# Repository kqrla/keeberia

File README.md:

# keeberia ☆.ᐟ

> a visual, parametric way to design custom macropads, keyboards, and other little physical input devices without manually rebuilding the same stuff every single time»

## what is this

keeberia is basically me trying to make the process of making a keyboard less annoying. <br>
for context, i loooove keyboards, and i've made end-to-end macropad pcbs + cases before, and while making them is really fun, there is also a very specific point each type where i'm like *"ugh. there's got to be a better way than this"* because so much of the process is repetitive, which, my adhd be damned, feels like walking on legos to me. i mean, come on, we

- have a layout.
- place switches.
- place their footprints.
- make the matrix.
- route it.
- then you go make a plate.
- then you go make a case.
- then you add screw holes.
- then you add standoffs.
- then you make sure the usb port isn't blocked.
- then you realize you changed the pcb layout.
- so now you have to go fix the case.
- and then you change the switch.
- and now the clearance is different.
- and then you have to fix something else.

none of these things are necessarily difficult individually. the annoying part is that the same information keeps having to be translated between different programs and rebuilt manually.

and keyboards are structured enough that a LOT of this could just be generated.

so... why not?

---

## the problem

custom keyboard design currently involves a weird collection of tools that each know about one part of the device.

you might use:

- kicad for the pcb
- fusion 360 / onshape / openscad / etc. for the case
- another thing for firmware
- another thing for keycap models
- spreadsheets for parts
- manufacturer tools for production
- random websites for component footprints and references

and then somehow the person making the keyboard is responsible for making sure all of those things agree with each other.

- the layout knows where the keys are.
- the pcb knows where the footprints are.
- the cad file knows where the case is.
- the keycap knows how tall it is.

but they don't necessarily know about each other.

so the human becomes the middleware.

which feels kind of silly when the relationships are often extremely predictable.

---

## the repetitive part

this is the part that really bothers me.

- a switch has a footprint.
- a switch has a known spacing.
- a 2u key has predictable geometry.
- an encoder has predictable mounting requirements.
- a display has predictable dimensions.
- a usb connector needs a predictable opening.
- a screw needs a hole.
- a standoff needs somewhere to go.
- a case needs clearance around the pcb.

these are not random artistic decisions.

they're relationships.

and computers are very good at relationships.

- if i move something, the other things that depend on it should know that i moved it.
- if i change my switch type, the pcb and case should know that too.
- if i make my pcb wider, my case should not sit there pretending it didn't happen.

---

## what keeberia is trying to do

keeberia is a design environment where you describe the device at a higher level and let the boring/repetitive parts get generated from that.

instead of starting with:

*"place footprint + assign net + route trace + draw wall + cut hole + measure clearance"*

you start with:

*"i want a 4x4 macropad"*

then:

- «this is a knob»
- «these two spaces are an eink display»
- «these are choc switches»
- «i want rgb»
- «i want a weird shaped pcb»
- «i want a chunky case»

and keeberia figures out how those decisions translate into the actual hardware.

---

# the five flows

keeberia is split into five major design flows.

they aren't meant to be five separate files or five completely separate programs.

they're five ways of looking at the same device.

```
layout
  ↓
components
  ↓
pcb
  ↓
case
  ↓
keys + knobs
```

but you can jump between them whenever you want.

- if you change something in components, the pcb and case should update.
- if you change the pcb shape, the case should react.
- if you change the keycap profile, the 3d preview should change.

the project is one object. the flows are just different views into it.

---

## the first flow — layout

this is the "where does everything go" part.

you can start with something like:

- 2x2
- 3x3
- 4x4
- numpad
- blank

or start blank and use a google-docs-style grid selector.

once you're in the editor, every space starts as a key.

```
□ □ □ □
□ □ □ □
□ □ □ □
```

you can drag-select cells, merge them, split them, or right click them and do something like:

```
switch to →
    key
    encoder
    knob
    oled
    eink
    joystick
    spacer
```

so if i select two cells and turn them into an eink display, keeberia knows that those two cells are now one physical region.

this stage is deliberately not pcb design.

i just want to figure out the shape and arrangement of the device first.

---

## the second flow — components

now we figure out what everything actually is.

the layout might know that something is a key.

components tells keeberia:

- "okay, this is a cherry mx switch"
- "this is a kailh choc v1"
- "this is an ec11 encoder"
- "this is a 128x64 oled"

this is where you choose things like:

- switch type
- hotswap / solder
- stabilizers
- encoder model
- display model
- controller
- rgb
- other hardware

the ui should feel very notion-ish here.

select one thing, or select 12 things, then change a property.

for example:

```
switch

[ cherry mx ]
[ choc v1 ]
[ choc v2 ]
[ gateron low profile ]
```

then:

```
mounting

[ solder ]
[ hotswap ]
```

then:

```
rgb

[ none ]
[ per-key ]
[ underglow ]
```

and if i select every key, i should be able to change all of them at once.

the important part is that users don't have to know the footprint implementation just to choose a component.

if i choose an ec11, keeberia should know what an ec11 requires.

---

## the third flow — pcb

this is where the abstract design becomes an actual board.

the user should be able to control things like:

- pcb shape
- rounded corners
- custom dxf outlines
- silkscreen
- text
- graphics
- logos
- front/back artwork

but i don't want the first experience to be:

"congratulations, here are 900 traces"

the repetitive pcb work should be generated from the component information.

keeberia already knows:

- where the switches are
- what switches they are
- where the encoder is
- what encoder it is
- where the display is
- what controller is being used

so it should be able to use that information to generate the pcb structure.

advanced users can still expose traces, vias, nets, etc.

i just don't want every person making a tiny macropad to have to manually deal with everything.

---

## the forth flow — case

this is probably where the whole idea gets even more useful.

cases are so repetitive.

a lot of them are basically some variation of:

```
pcb
+
clearance
+
walls
+
mounting
+
cutouts
```

so instead of manually modeling the whole thing every time, keeberia should generate the geometry parametrically.

you choose things like:

- tray mount
- sandwich
- top mount
- integrated plate
- wall thickness
- pcb margin
- front/rear height
- typing angle
- screw type
- heatset inserts
- usb cutout
- reset access
- feet

and the case updates.

- if the pcb changes, the case changes.
- if the encoder moves, its opening moves.
- if the usb moves, the cutout moves.

that's the whole point.

---

## 05 — keys + knobs

and then we get to the fun part.

this is basically:

«okay now make the thing look and feel how i actually want it to»

choose keycap profiles:

- cherry
- oem
- dsa
- xda
- sa
- mt3
- choc

choose legends. choose knob styles. change knob diameter/height.

and see the actual finished device in the preview.

---

## the preview

the preview is not just some little thumbnail in the corner.

i want the device to basically live in the middle of the application.

there should be a 2d and 3d view.

2d is useful for:

- layout
- pcb
- silkscreen
- case dimensions
- exact placement

3d is useful for:

- case shape
- component clearance
- keycap profiles
- knobs
- overall appearance

and then there can be an exploded view:

```
keycaps
↓
switches
↓
plate
↓
pcb
↓
case
```

so you can actually see how the thing goes together.

the preview should be powered by the same underlying project data as the generators, so it isn't just a pretty fake rendering.

---

## the part i care about most

keeberia should understand that these things are related.

if i change:

```
mx → choc
```

that can affect:

- footprint
- plate
- switch height
- keycap clearance
- case height

if i change:

```
3x3 → 4x3
```

that can affect:

- pcb dimensions
- case dimensions
- mounting locations
- plate
- preview

if i move an encoder:

- its pcb footprint moves
- its case opening moves
- its knob moves in 3d

i don't want to manually tell five different programs that i moved something.

that's what the project model is for.

---

## under the hood

**autorouting is a two-rung ladder.** rung one is circuitron's own a* router — fast, in-process, deterministic. when a board is too dense for it, the worker escalates to [freerouting](https://freerouting.org) (open source, battle-tested push-and-shove) through a dsn/ses bridge: the board exports to specctra dsn at kicad's exact conventions, freerouting routes it headless, and the ses session imports back into the engine's own segment/via model — then judged by the same drc as the engine's routes. wire it up with `FREEROUTING_BIN` (jar or binary) and optional `FREEROUTING_JAVA` + `FREEROUTING_TIMEOUT_MS`; the rung is skipped cleanly when unset.

**all rendering happens on the viewer's hardware.** previews are client-side webgl/three.js computed from the same project model the generators consume — the server never touches a gpu.

keeberia isn't trying to reinvent every existing hardware tool.

it's more like a layer on top of them.

for pcb generation, the target is kicad-compatible output and eventually things like:

- kicad projects
- gerbers
- drill files
- bom
- pick-and-place files

for cad:

- openscad (parametric, printable — the tradeoffs are on record in [backend/cad/stack/tradeoffs.md](backend/cad/stack/tradeoffs.md))
- stl
- 3mf
- dxf

for the browser preview:

- three.js / webgl

the idea is basically:

```
my design
    ↓
keeberia project model
    ↓
pcb / cad / manufacturing / preview
```

rather than manually keeping all of those things synchronized.

---

## why start with keyboards?

because this is a really good problem to attack with software.

the keyboard ecosystem is already incredibly modular.

you have:

- switches
- keycaps
- pcbs
- plates
- cases
- encoders
- displays
- controllers
- leds
- stabilizers
- knobs
- cables
- artisan parts
- diy kits
- 3d printed parts
- cnc parts

people are already designing and buying all of these things.

there's a huge amount of customization happening.

and yet the actual design workflow still involves a lot of manual work.

that's kind of the opportunity.

---

## and it doesn't have to stay keyboards

the more i think about it, the less this is really a "keyboard tool."

a macropad is just one example of a customizable physical input device.

the same system could eventually work for:

- midi controllers
- stream deck-style devices
- simulator panels
- synth controllers
- custom desktop controllers
- accessibility interfaces
- maker electronics
- weird little one-off control panels

the common thing is basically:

```
inputs
+
electronics
+
physical layout
+
enclosure
```

which is exactly the kind of thing a parametric system can handle.

---

## what i want keeberia to feel like

- not kicad in a browser.
- not fusion 360 but worse.
- not another form where i have to enter 700 dimensions.

i want it to feel like:

"i have a weird little device idea"

and then i can just start making it.

- drag some squares around.
- turn one into a knob.
- merge two into a display.
- pick some switches.
- draw a weird pcb shape.
- make a case.
- put stupid little keycaps on it.
- rotate it in 3d.

then eventually hit:

export

and get the actual files needed to build the thing.

because if the computer can already figure out the boring, repetitive relationships between all of these parts, i would much rather let it do that and spend my time on the parts that are actually fun.

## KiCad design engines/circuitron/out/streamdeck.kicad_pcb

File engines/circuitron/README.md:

# circuitron

**circuitron** — the pcb + schematic engine. the deterministic pcb generator. typescript, zero runtime deps. **no ai anywhere in here** — same layout in, same board out, every time.

## fab rules drive the board

the generator's clearances and drc thresholds come from the fab's evidence
record, `research/manufacturing/capabilities/<id>.json`. pass a fab and the
board is generated and checked against that fab's published floors:

```ts
generatePcb(layout, "engine", { id: "jlcpcb", record: jlcpcbJson })
```

rules of the road:

- no fab selected = the engine's own floors, the pre-fab behaviour exactly
- a fab never loosens the engine, only tightens it. route constants clamp to
  engine floors so validated boards do not move silently, while drc
  thresholds take the fab's real published numbers (spacing, edge, trace
  width, via annular ring, plate drills) and the outline is measured against
  the fab's panel window
- the engine stays pure: it never reads files, the caller passes the record
- the first thing this caught: engine vias were 0.7mm over a 0.35mm drill, a
  0.175mm annular ring, under jlcpcb's own 0.20 minimum. vias are now 0.85mm
  (0.25 annular) and the engine drc refuses anything thinner

`test/fab.ts` runs all five fab records against all four reference boards.

## independent verification

`test/kicad_drc.ts` asks `kicad-cli` for a second opinion on the exported
board. it runs on the server/ci image only and skips cleanly when the binary
is absent. nobody using keeberia needs kicad: the browser sends a layout, the
daemon generates, and this gate runs before a human can order the artifacts.

## structure vs taste, and the downloads

the pipeline knows two kinds of input. structure (placements, nets, copper,
clearances) is engine owned and verified. taste (silhouette as rect, polygon
or uploaded dxf, decorative cutouts, silkscreen art) is user owned and
validated against the same fab record, never allowed to loosen a rule. see
`docs/pcb-artifacts.md` for the seam.

three downloads come out of every board: `.step` (planar brep, verified by
reading it back through occt), `.glb` (glTF 2.0, metres), `.stl` (binary,
millimetres). `src/step.ts`, `src/mesh3d.ts`.

## pipeline

```
keeberia layout json
  → layout.ts     placement: grid cells → components, mcu, holes, outline bbox
  → netlist.ts    direct-gpio or diode-matrix fallback, i2c/encoder budgets
  → route.ts      fan-out stubs + negotiated-congestion a* (0.5mm grid, keepouts, vias)
  → kicad.ts      kicad 8 .kicad_pcb export (s-expressions via sexp.ts)
  → drc.ts       pad clearance, shorts, edge, unrouted nets
  → bom.ts        bom csv        → silkscreen.ts   → preview.ts (svg)
```

entry: `generatePcb(layout, router?, fab?)` → `{ kicadPcb, bom, qmkInfo, result, fab }` (see `src/index.ts`).

## run tests

```bash
cd engines/circuitron
npx tsx test/run.ts        # 3 boards: hackpad-3key, ninepad, streamdeck → out/
npx tsx test/validate.ts   # s-expression balance + net/pad reference checks
npx tsx test/render.ts     # svg renders
```

## source layout

- `src/footprints.ts` — **the only place pad geometry lives**, verified against kicad official / hackclub care package / perigoso. provenance in `../research/`
- `src/types.ts` — layout schema + internal types (FootprintDef, Placement, Net…)
- `test/layouts.ts` — the three reference layouts (hackpad-3key, ninepad, streamdeck); regression fixtures — the autolayout daemon smoke-tests against these too

## rules

- new parts get footprint-verified (three sources or datasheet) **before** entering `footprints.ts`
- the router never gets to leave the board edge (0.45mm inside) — drc and router agree on this
- output determinism is a feature: no timestamps, no randomness, no map-iteration-order leaks

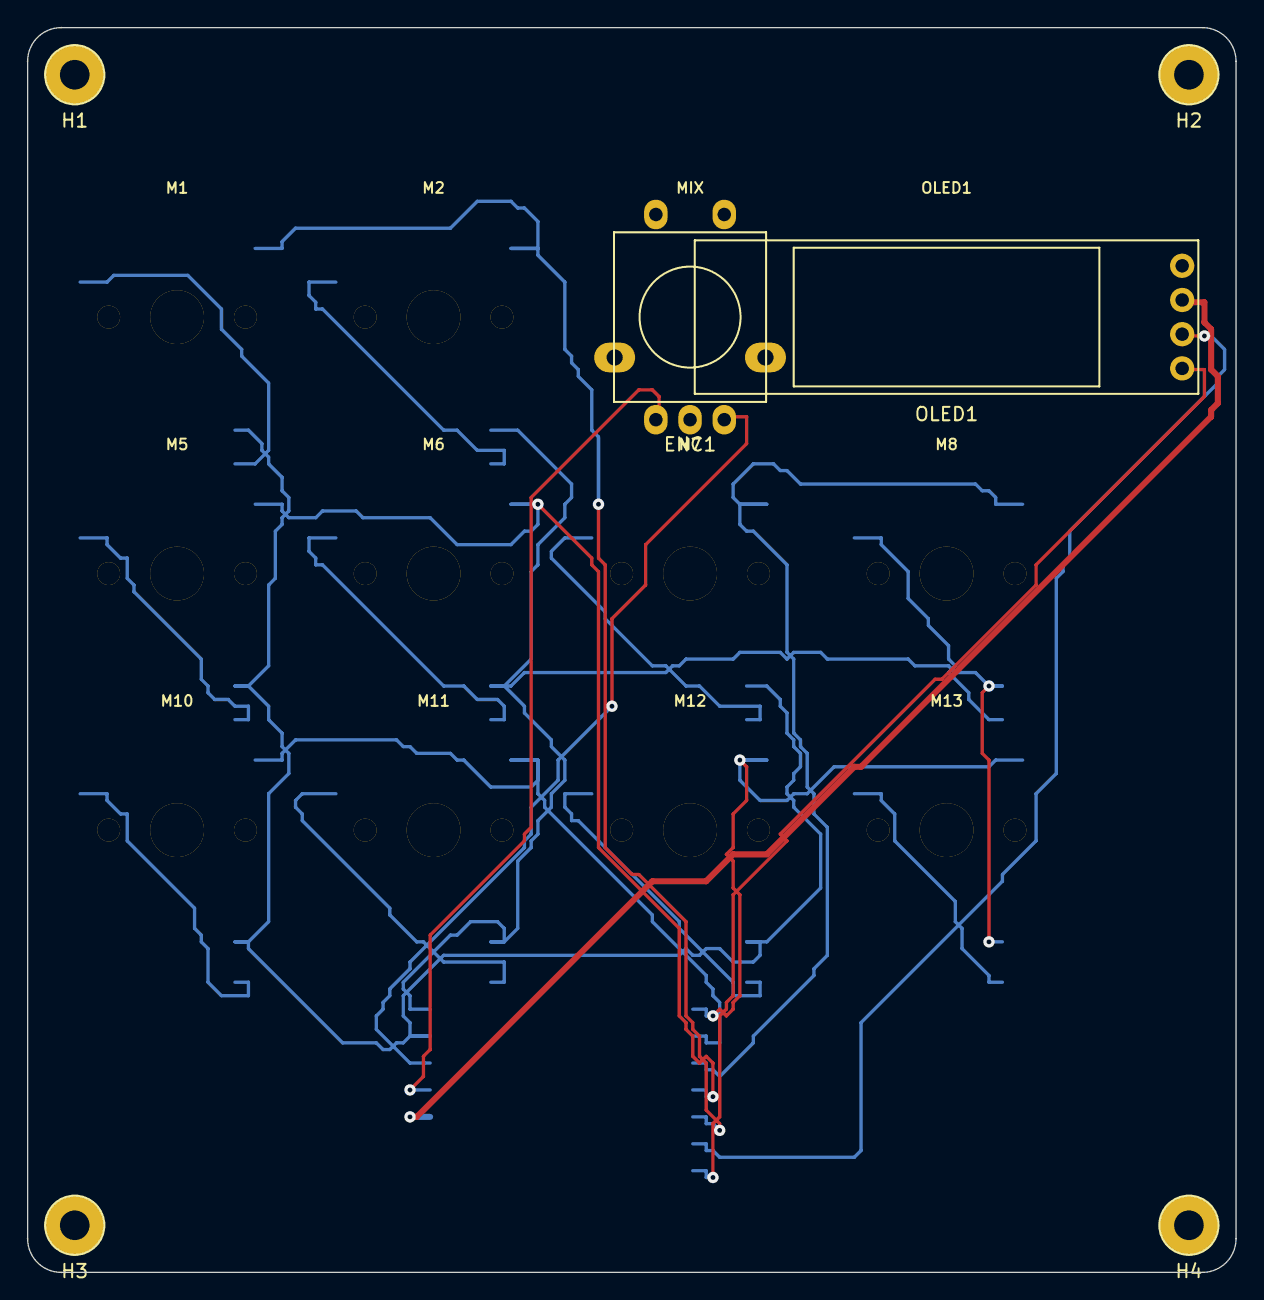
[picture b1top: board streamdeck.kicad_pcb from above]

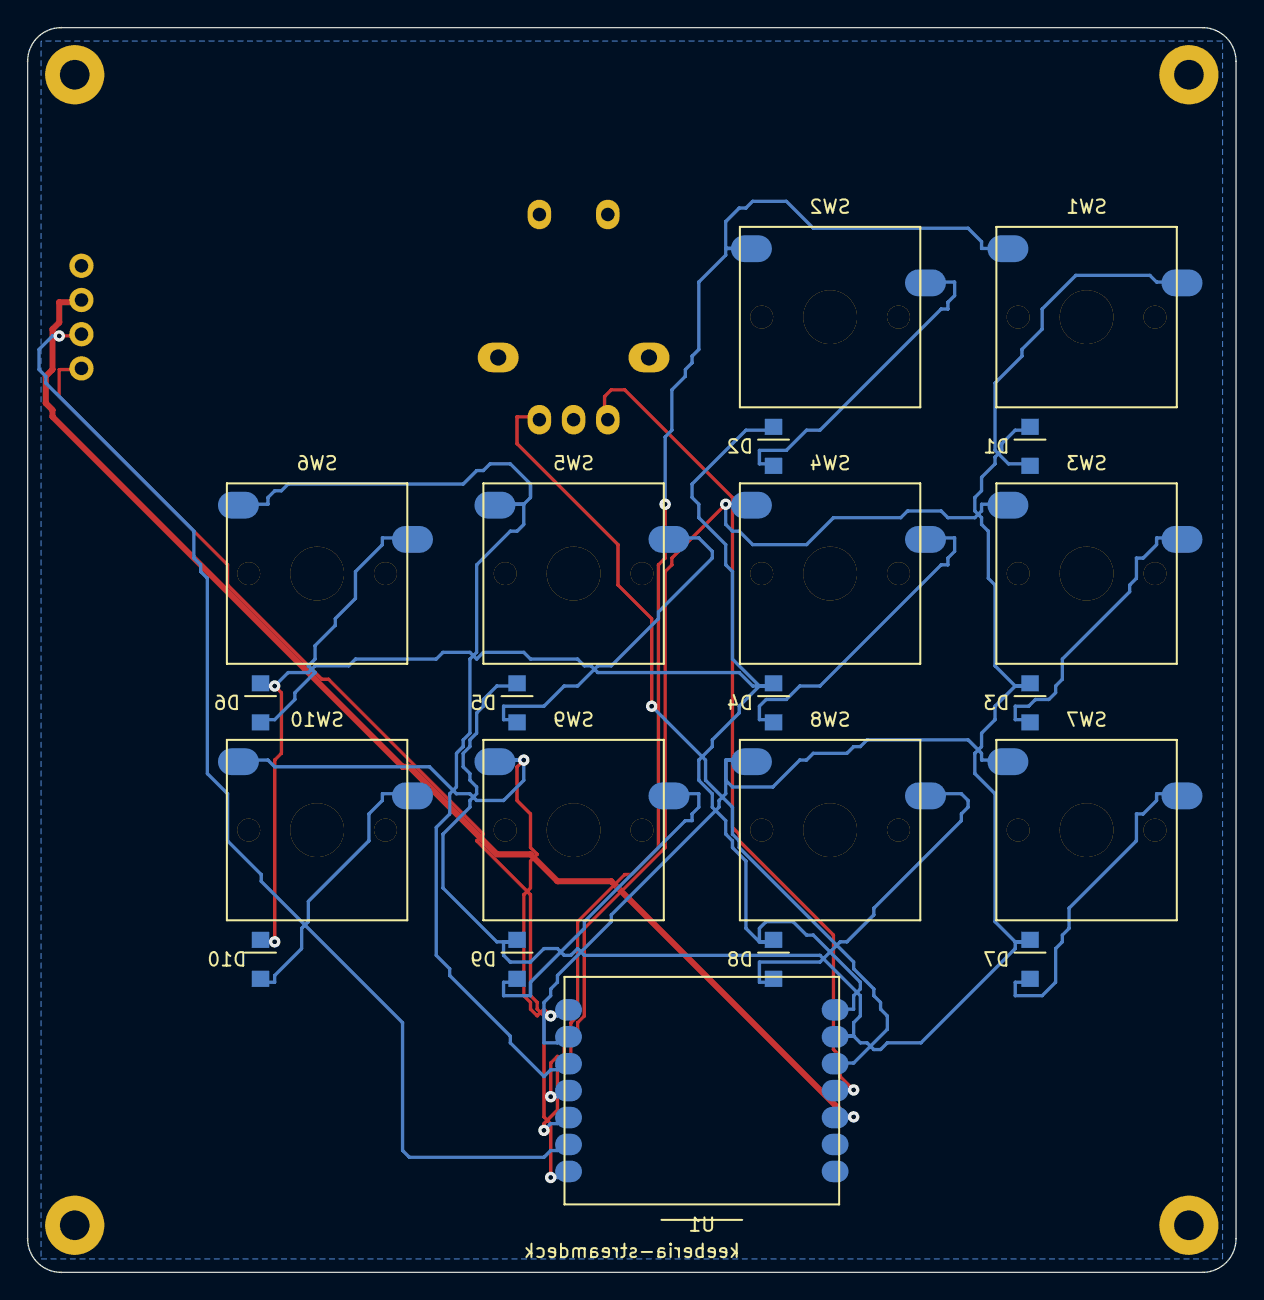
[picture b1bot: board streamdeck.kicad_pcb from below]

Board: 2 copper layers, 89.8 x 92.5 mm, 27 parts (21 on the bottom side), 23 nets.

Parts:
D1, D2, D3, D4, D5, D6, D7, D8, D9, D10: 1N4148W; D_SOD-123
ENC1: MIX; RotaryEncoder_Alps_EC11-Switched_Vertical
H1, H2, H3, H4: M2; MountingHole_2.2mm_M2
OLED1: SSD1306 0.91in I2C; Display_SSD1306_128x32_0.91in
SW1: M1; SW_Cherry_MX_Hotswap_1.00u_PCB
SW2: M2; SW_Cherry_MX_Hotswap_1.00u_PCB
SW3: M5; SW_Cherry_MX_Hotswap_1.00u_PCB
SW4: M6; SW_Cherry_MX_Hotswap_1.00u_PCB
SW5: M7; SW_Cherry_MX_Hotswap_1.00u_PCB
SW6: M8; SW_Cherry_MX_Hotswap_1.00u_PCB
SW7: M10; SW_Cherry_MX_Hotswap_1.00u_PCB
SW8: M11; SW_Cherry_MX_Hotswap_1.00u_PCB
SW9: M12; SW_Cherry_MX_Hotswap_1.00u_PCB
SW10: M13; SW_Cherry_MX_Hotswap_1.00u_PCB
U1: Seeed XIAO RP2040; Module_Seeed_XIAO

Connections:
+3V3: OLED1.VCC, U1.3V3
COL0: SW1.1, SW2.1, U1.D6
COL1: SW3.1, SW4.1, U1.D7
COL2: SW5.1, SW6.1, U1.D8
COL3: SW7.1, SW8.1, U1.D9
COL4: SW9.1, SW10.1, U1.D10
ENC1_A: ENC1.A, U1.D0
ENC1_B: ENC1.B, U1.D1
GND: ENC1.C, ENC1.MP1, ENC1.MP2, OLED1.GND, U1.GND
N_SW1: D1.A, SW1.2
N_SW2: D2.A, SW2.2
N_SW3: D3.A, SW3.2
N_SW4: D4.A, SW4.2
N_SW5: D5.A, SW5.2
N_SW6: D6.A, SW6.2
N_SW7: D7.A, SW7.2
N_SW8: D8.A, SW8.2
N_SW9: D9.A, SW9.2
N_SW10: D10.A, SW10.2
ROW0: D1.K, D3.K, D5.K, D7.K, D9.K, U1.D2
ROW1: D2.K, D4.K, D6.K, D8.K, D10.K, U1.D3
SCL: OLED1.SCL, U1.D5
SDA: OLED1.SDA, U1.D4

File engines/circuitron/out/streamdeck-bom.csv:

Ref(s),Value,Footprint,Qty
"SW1","M1","keeberia:SW_Cherry_MX_Hotswap_1.00u_PCB","1"
"SW2","M2","keeberia:SW_Cherry_MX_Hotswap_1.00u_PCB","1"
"ENC1","MIX","keeberia:RotaryEncoder_Alps_EC11-Switched_Vertical","1"
"OLED1","SSD1306 0.91in I2C","keeberia:Display_SSD1306_128x32_0.91in","1"
"SW3","M5","keeberia:SW_Cherry_MX_Hotswap_1.00u_PCB","1"
"SW4","M6","keeberia:SW_Cherry_MX_Hotswap_1.00u_PCB","1"
"SW5","M7","keeberia:SW_Cherry_MX_Hotswap_1.00u_PCB","1"
"SW6","M8","keeberia:SW_Cherry_MX_Hotswap_1.00u_PCB","1"
"SW7","M10","keeberia:SW_Cherry_MX_Hotswap_1.00u_PCB","1"
"SW8","M11","keeberia:SW_Cherry_MX_Hotswap_1.00u_PCB","1"
"SW9","M12","keeberia:SW_Cherry_MX_Hotswap_1.00u_PCB","1"
"SW10","M13","keeberia:SW_Cherry_MX_Hotswap_1.00u_PCB","1"
"U1","Seeed XIAO RP2040","keeberia:Module_Seeed_XIAO","1"
"D1, D10, D2, D3, D4, D5, D6, D7, D8, D9","1N4148W","keeberia:D_SOD-123","10"

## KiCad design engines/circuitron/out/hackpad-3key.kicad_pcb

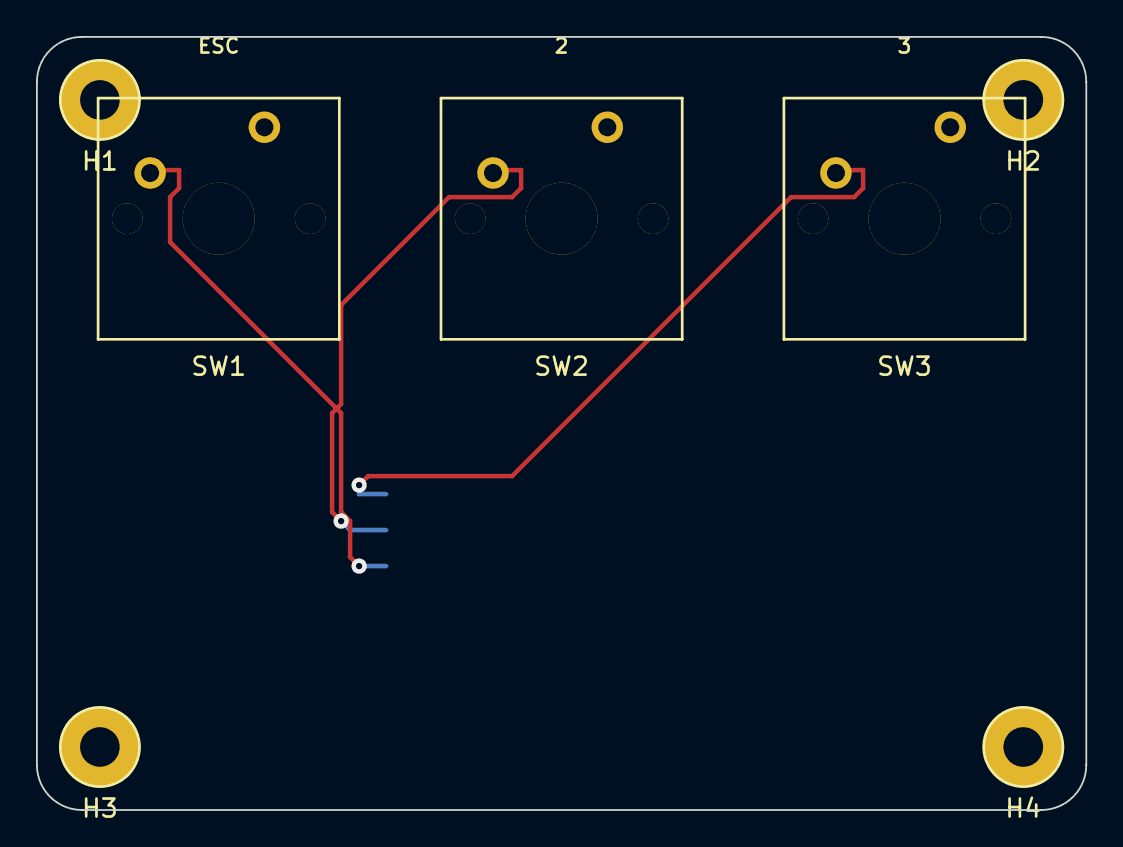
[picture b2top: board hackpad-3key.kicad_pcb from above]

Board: 2 copper layers, 58.3 x 43.0 mm, 8 parts (1 on the bottom side), 4 nets.

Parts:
H1, H2, H3, H4: M2; MountingHole_2.2mm_M2
SW1: ESC; SW_Cherry_MX_1.00u_PCB_solder
SW2: 2; SW_Cherry_MX_1.00u_PCB_solder
SW3: 3; SW_Cherry_MX_1.00u_PCB_solder
U1: Seeed XIAO RP2040; Module_Seeed_XIAO

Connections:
GND: SW1.2, SW2.2, SW3.2, U1.GND
K1: SW1.1, U1.D0
K2: SW2.1, U1.D1
K3: SW3.1, U1.D2

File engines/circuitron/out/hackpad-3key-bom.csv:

Ref(s),Value,Footprint,Qty
"SW1","ESC","keeberia:SW_Cherry_MX_1.00u_PCB_solder","1"
"SW2","2","keeberia:SW_Cherry_MX_1.00u_PCB_solder","1"
"SW3","3","keeberia:SW_Cherry_MX_1.00u_PCB_solder","1"
"U1","Seeed XIAO RP2040","keeberia:Module_Seeed_XIAO","1"

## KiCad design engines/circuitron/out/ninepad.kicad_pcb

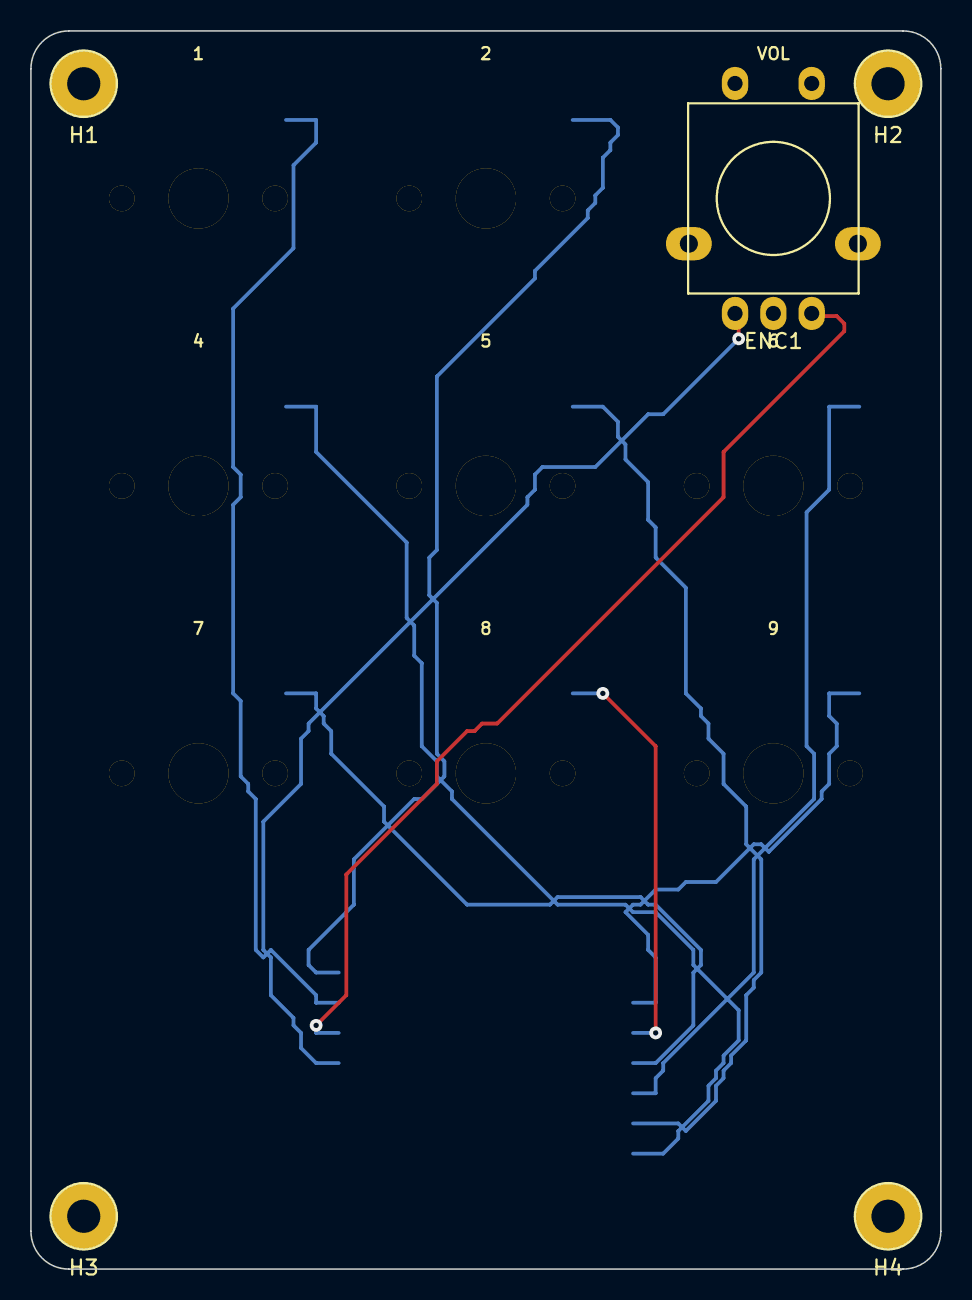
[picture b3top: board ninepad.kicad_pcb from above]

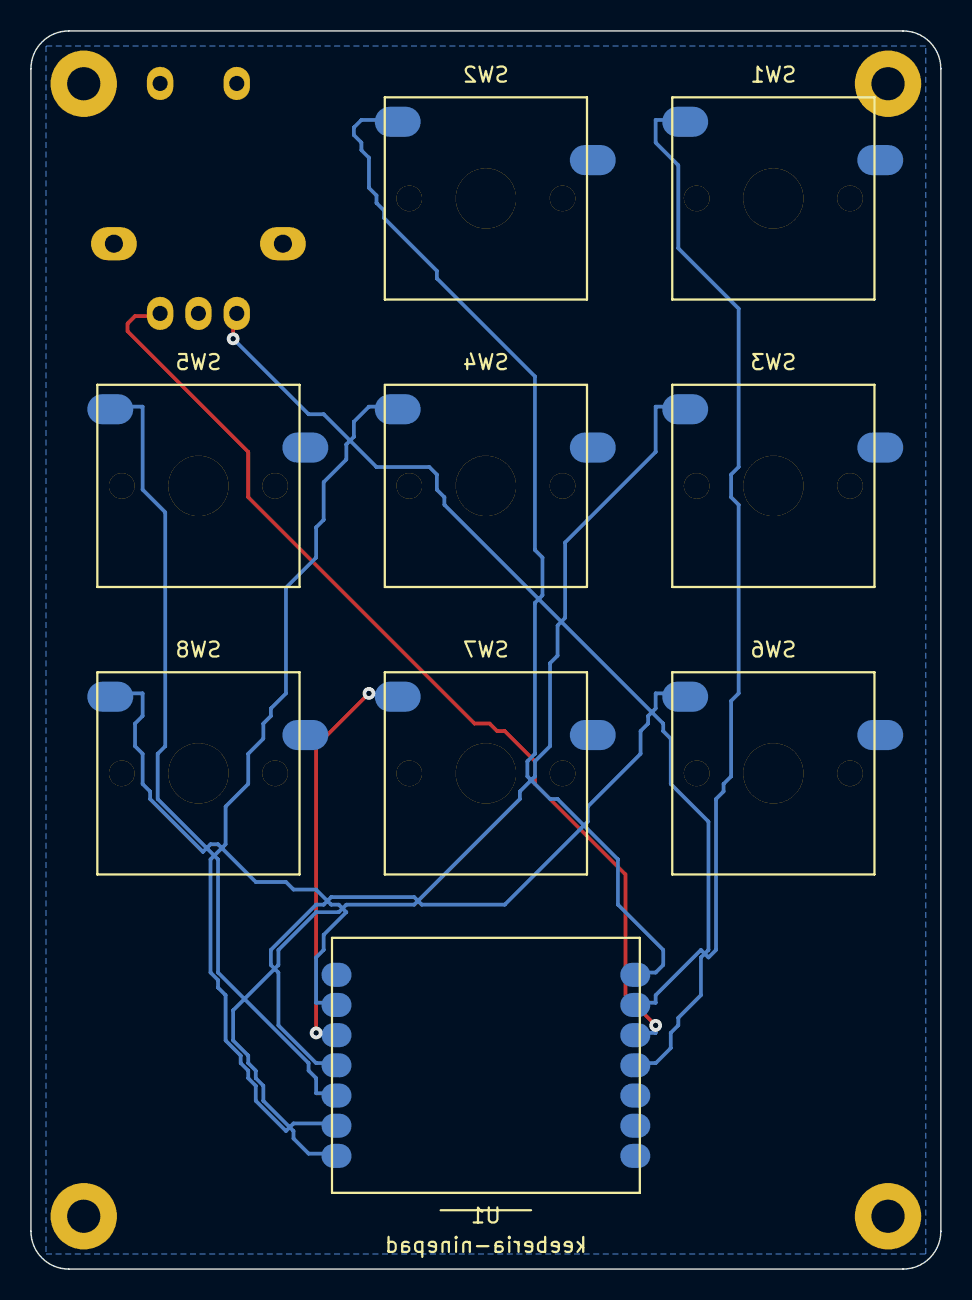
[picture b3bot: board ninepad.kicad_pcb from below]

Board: 2 copper layers, 60.3 x 82.0 mm, 14 parts (9 on the bottom side), 11 nets.

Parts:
ENC1: VOL; RotaryEncoder_Alps_EC11-Switched_Vertical
H1, H2, H3, H4: M2; MountingHole_2.2mm_M2
SW1: 1; SW_Cherry_MX_Hotswap_1.00u_PCB
SW2: 2; SW_Cherry_MX_Hotswap_1.00u_PCB
SW3: 4; SW_Cherry_MX_Hotswap_1.00u_PCB
SW4: 5; SW_Cherry_MX_Hotswap_1.00u_PCB
SW5: 6; SW_Cherry_MX_Hotswap_1.00u_PCB
SW6: 7; SW_Cherry_MX_Hotswap_1.00u_PCB
SW7: 8; SW_Cherry_MX_Hotswap_1.00u_PCB
SW8: 9; SW_Cherry_MX_Hotswap_1.00u_PCB
U1: Seeed XIAO RP2040; Module_Seeed_XIAO

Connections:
ENC1_A: ENC1.A, U1.D0
ENC1_B: ENC1.B, U1.D1
GND: ENC1.C, ENC1.MP1, ENC1.MP2, SW1.2, SW2.2, SW3.2, SW4.2, SW5.2, SW6.2, SW7.2, SW8.2, U1.GND
K1: SW1.1, U1.D2
K2: SW2.1, U1.D3
K3: SW3.1, U1.D4
K4: SW4.1, U1.D5
K5: SW5.1, U1.D6
K6: SW6.1, U1.D7
K7: SW7.1, U1.D8
K8: SW8.1, U1.D9

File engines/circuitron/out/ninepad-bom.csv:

Ref(s),Value,Footprint,Qty
"SW1","1","keeberia:SW_Cherry_MX_Hotswap_1.00u_PCB","1"
"SW2","2","keeberia:SW_Cherry_MX_Hotswap_1.00u_PCB","1"
"ENC1","VOL","keeberia:RotaryEncoder_Alps_EC11-Switched_Vertical","1"
"SW3","4","keeberia:SW_Cherry_MX_Hotswap_1.00u_PCB","1"
"SW4","5","keeberia:SW_Cherry_MX_Hotswap_1.00u_PCB","1"
"SW5","6","keeberia:SW_Cherry_MX_Hotswap_1.00u_PCB","1"
"SW6","7","keeberia:SW_Cherry_MX_Hotswap_1.00u_PCB","1"
"SW7","8","keeberia:SW_Cherry_MX_Hotswap_1.00u_PCB","1"
"SW8","9","keeberia:SW_Cherry_MX_Hotswap_1.00u_PCB","1"
"U1","Seeed XIAO RP2040","keeberia:Module_Seeed_XIAO","1"

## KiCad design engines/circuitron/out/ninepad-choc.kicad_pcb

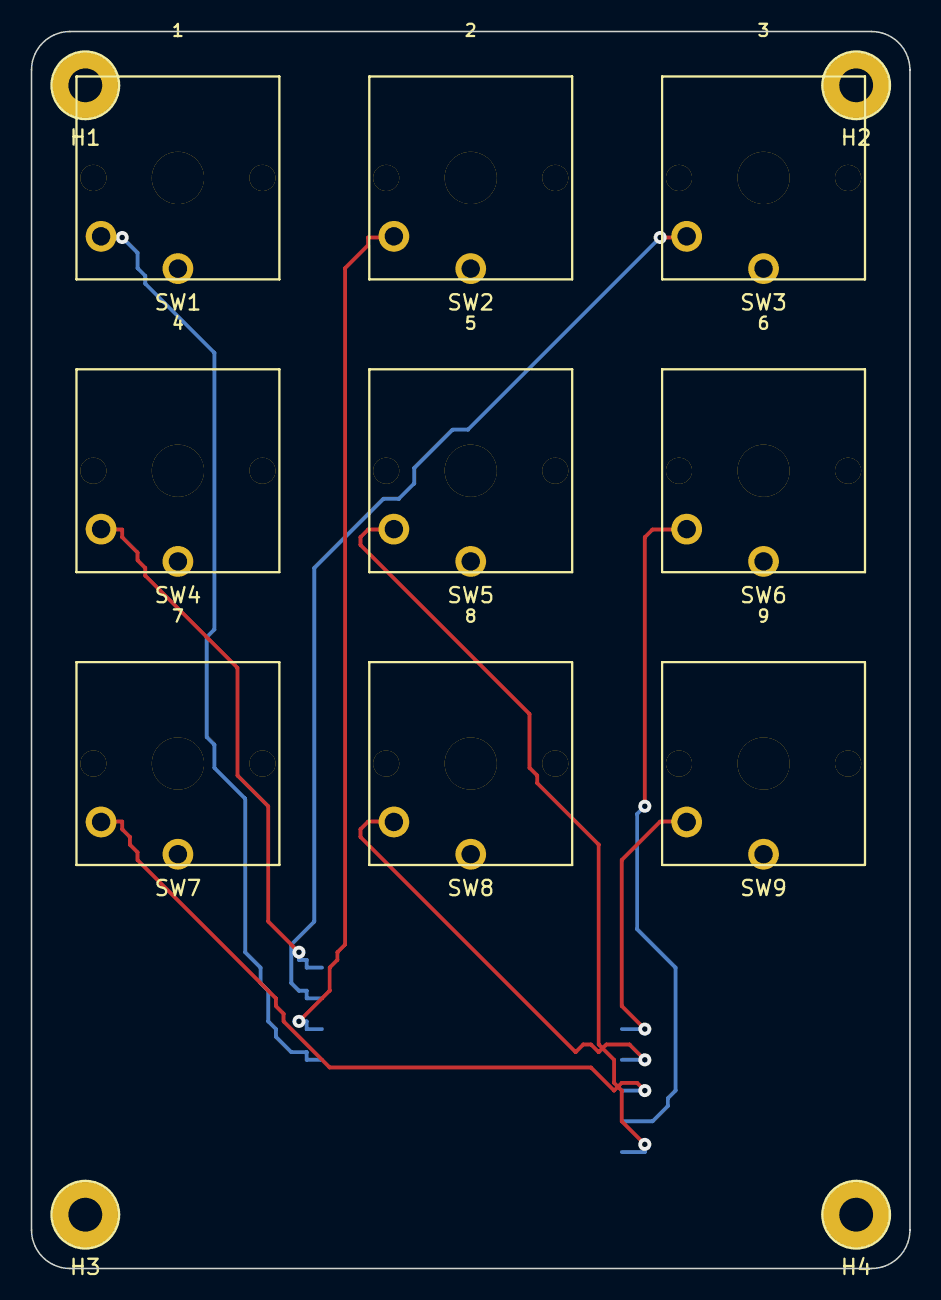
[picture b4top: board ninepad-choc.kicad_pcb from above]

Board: 2 copper layers, 57.1 x 80.5 mm, 14 parts (1 on the bottom side), 10 nets.

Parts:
H1, H2, H3, H4: M2; MountingHole_2.2mm_M2
SW1: 1; SW_Kailh_Choc_V1
SW2: 2; SW_Kailh_Choc_V1
SW3: 3; SW_Kailh_Choc_V1
SW4: 4; SW_Kailh_Choc_V1
SW5: 5; SW_Kailh_Choc_V1
SW6: 6; SW_Kailh_Choc_V1
SW7: 7; SW_Kailh_Choc_V1
SW8: 8; SW_Kailh_Choc_V1
SW9: 9; SW_Kailh_Choc_V1
U1: Seeed XIAO RP2040; Module_Seeed_XIAO

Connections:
GND: SW1.2, SW2.2, SW3.2, SW4.2, SW5.2, SW6.2, SW7.2, SW8.2, SW9.2, U1.GND
K1: SW1.1, U1.D0
K2: SW2.1, U1.D1
K3: SW3.1, U1.D2
K4: SW4.1, U1.D3
K5: SW5.1, U1.D4
K6: SW6.1, U1.D5
K7: SW7.1, U1.D6
K8: SW8.1, U1.D7
K9: SW9.1, U1.D8

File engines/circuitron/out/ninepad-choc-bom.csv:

Ref(s),Value,Footprint,Qty
"SW1","1","keeberia:SW_Kailh_Choc_V1","1"
"SW2","2","keeberia:SW_Kailh_Choc_V1","1"
"SW3","3","keeberia:SW_Kailh_Choc_V1","1"
"SW4","4","keeberia:SW_Kailh_Choc_V1","1"
"SW5","5","keeberia:SW_Kailh_Choc_V1","1"
"SW6","6","keeberia:SW_Kailh_Choc_V1","1"
"SW7","7","keeberia:SW_Kailh_Choc_V1","1"
"SW8","8","keeberia:SW_Kailh_Choc_V1","1"
"SW9","9","keeberia:SW_Kailh_Choc_V1","1"
"U1","Seeed XIAO RP2040","keeberia:Module_Seeed_XIAO","1"
